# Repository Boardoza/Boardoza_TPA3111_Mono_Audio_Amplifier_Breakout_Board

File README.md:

# Boardoza TPA3111 Mono Audio Amplifier Breakout Board

The **Boardoza TPA3111 Mono Audio Amplifier Module** is a compact and efficient Class-D audio amplifier built around the **Texas Instruments TPA3111D1** chip. Designed to deliver up to **10W mono output power**, this board provides high-quality audio performance with minimal heat generation thanks to its high-efficiency architecture.

With a wide **8V to 28V DC input voltage range**, this amplifier module is compatible with a variety of power sources including DC adapters and battery systems. Screw terminal connections for power, audio input, and speaker output make installation quick and reliable. It is ideal for **DIY speaker builds, portable audio systems, embedded audio solutions, and custom sound projects** requiring compact and efficient amplification.

## [Click here to purchase!](https://www.ozdisan.com/ureticiler/boardoza)

| Front Side | Back Side |
|:---:|:---:|
|  |  |

---

## Key Features

- **High-Efficiency Class-D Amplifier:** 310 khz Switching frequency provides clear and powerful mono audio output with minimal heat generation.
- **Wide Input Voltage Range:** Operates from 8V to 28V DC, compatible with various power sources.
- **Easy Connectivity:** Screw terminals for audio input, speaker output, and power connections.
- **Clean Audio Performance:** Integrated pop and click suppression for smooth startup and shutdown.
- **Built-in Protection Features:** Includes thermal shutdown and short-circuit protection for reliable operation.

---

## Technical Specifications

**Model:** TPA3111D1  
**Manufacturer:** Boardoza   
**Manufacturer IC:** Texas Instruments   
**Input Voltage:** 8V – 28V DC  
**Functions:** Mono Audio Amplifier  
**Amplifier Type:** Class-D  
**Output Power:** Up to 10W  
**Efficiency:** Up to 90%  
**Audio Output:** Mono (H-Bridge)  
**Gain Setting:** Configurable via JP2 / JP3 (Default: 36 dB)  
**Protection Features:** Thermal protection, short-circuit protection  
**Operating Temperature:** -40 °C to +85 °C  
**Board Dimensions:** 40 mm x 40 mm  

---

## Board Pinout

### **( JP2 & JP3 ) Gain Configuration (GAIN1 / GAIN0)**

| Pin / Jumper | Pin Name | Description |
|:---:|:---:|---|
| JP2 | GAIN1 | Gain select input (logic level via jumper) |
| JP3 | GAIN0 | Gain select input (logic level via jumper) |

> Default configuration is typically **36 dB** (GAIN1=1, GAIN0=1).

#### **Gain / Input Impedance Selection Table**

| GAIN1 | GAIN0 | Amplifier Gain (dB) (Typical) | Input Impedance (kΩ) (Typical) |
|:---:|:---:|:---:|:---:|
| 0 | 0 | 20 | 60 |
| 0 | 1 | 26 | 30 |
| 1 | 0 | 32 | 15 |
| 1 | 1 | 36 | 9 |

---

### **( JP5 ) Control Pins**

| Pin Number | Pin Name | Description |
|:---:|:---:|---|
| 1 | SD | Shutdown pin (Active Low). Connect to FAULT for auto-recovery |
| 2 | FAULT | Fault indicator pin (Active Low). Connect to SD for auto-recovery |

---

### **( J3 ) Power Connector**

| Pin Number | Pin Name | Description |
|:---:|:---:|---|
| 1 | 8V–28V | DC Voltage Input |
| 2 | GND | Ground |

---

### **( J1 ) Audio Input**

| Pin Number | Pin Name | Description |
|:---:|:---:|---|
| 1 | IN+ | Positive audio input |
| 2 | IN- | Negative audio input |

---

### **( J2 ) Speaker Output**

| Pin Number | Pin Name | Description |
|:---:|:---:|---|
| 1 | OUT+ | Class-D H-Bridge positive output |
| 2 | OUT- | Class-D H-Bridge negative output |

---

## Board Dimensions

---

## Step Files

[Boardoza TPA3111.step](./assets/TPA3111%20Step.step)

---

## Datasheet

[TPA3111D1 Datasheet](./assets/TPA3111%20Datasheet.pdf)

---

## Version History

- **V1.0.0** – Initial Release

---

## Support

- If you have any questions or need support, please contact **support@boardoza.com**

---

## **License**
### **Hardware Design**

[![CC BY-SA 4.0][cc-by-sa-shield]][cc-by-sa]

All hardware design files are licensed under [Creative Commons Attribution-ShareAlike 4.0 International License][cc-by-sa].

[cc-by-sa]: http://creativecommons.org/licenses/by-sa/4.0/
[cc-by-sa-shield]: https://img.shields.io/badge/License-CC%20BY--SA%204.0-lightgrey.svg

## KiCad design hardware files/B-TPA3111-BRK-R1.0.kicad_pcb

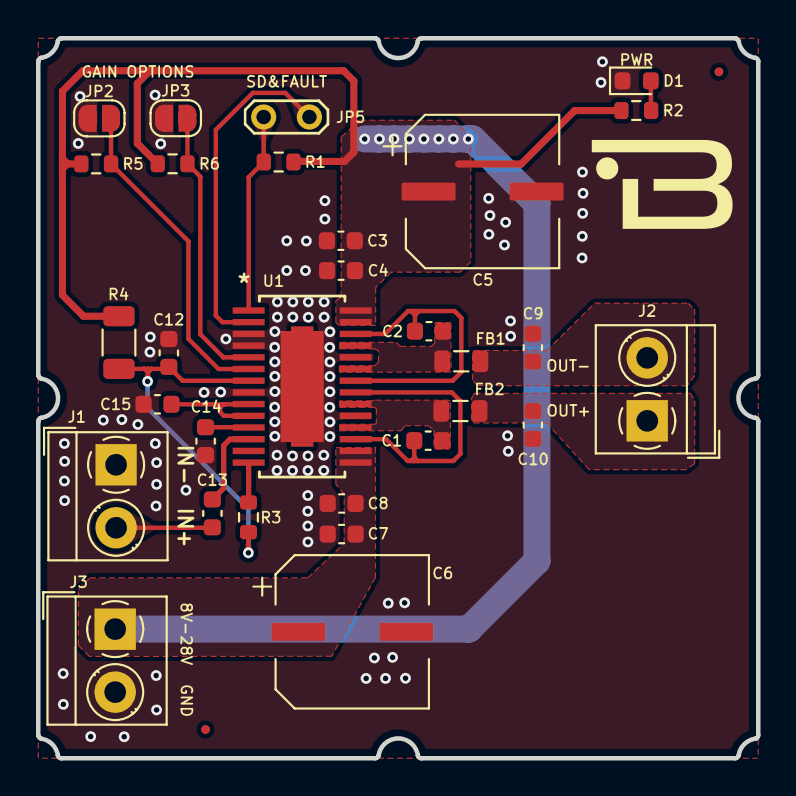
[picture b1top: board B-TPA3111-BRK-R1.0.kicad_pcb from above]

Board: 2 copper layers, 40.0 x 40.0 mm, 30 parts (0 on the bottom side), 19 nets.

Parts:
C1, C2: 0.47uF; C_0603_1608Metric
C3, C7: 0.1uF; C_0603_1608Metric
C4, C8, C9, C10: 1000pF; C_0603_1608Metric
C5, C6: 100uF; CP_Elec_8x10
C12, C13, C14, C15: 1uF; C_0603_1608Metric
D1: RED; LED_0603_1608Metric
FB1, FB2: 120R/100MHz; L_0805_2012Metric
J1, J2, J3: Screw_Terminal_01x02; TerminalBlock_MetzConnect_Type059_RT06302HBWC_1x02_P3.50mm_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
JP2, JP3: SolderJumper_2_Open; SolderJumper-2_P1.3mm_Open_RoundedPad1.0x1.5mm
JP5: Jumper_2_Open; TestPoint_2Pads_Pitch2.54mm_Drill0.8mm
R1, R3, R5, R6: 100K; R_0603_1608Metric
R2: 3K; R_0603_1608Metric
R4: 10R; R_1206_3216Metric
U1: TPA3111D1PWPR; PWP28_6P17X2P4-M

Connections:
/AVCC: C12.1, R3.1, R4.2, U1.7 (AVCC)
/GAIN0: JP3.1 (A), R6.1, U1.5 (GAIN0)
/GAIN1: JP2.1 (A), R5.1, U1.6 (GAIN1)
/GVDD: C15.1, U1.9 (GVDD), U1.10 (PLIMIT)
/INP: C13.2, U1.12 (INP)
/OUT+: C10.1, FB2.2, J2.1
/OUT-: C9.2, FB1.2, J2.2
/PVCC: C3.1, C4.1, C5.1, C6.1, C7.1, C8.1, J3.1, R1.1, R2.2, R4.1, R5.2, R6.2, U1.15 (PVCC), U1.16 (PVCC), U1.27 (PVCC), U1.28 (PVCC)
GND: C3.2, C4.2, C5.2, C6.2, C7.2, C8.2, C9.1, C10.2, C12.2, C14.1, C15.2, D1.1 (K), J1.1, J3.2, JP2.2 (B), JP3.2 (B), U1.3 (GND), U1.4 (GND), U1.8 (AGND), U1.19 (PGND), U1.24 (PGND), U1.29 (EPAD)
unnamed: C1.1, FB2.1, U1.18 (OUTP), U1.20 (OUTP)
unnamed: C1.2, U1.17 (BSP), U1.21 (BSP)
unnamed: C2.1, FB1.1, U1.23 (OUTN), U1.25 (OUTN)
unnamed: C2.2, U1.22 (BSN), U1.26 (BSN)
unnamed: D1.2 (A), R2.1
unnamed: C13.1, J1.2
unnamed: JP5.1 (A), U1.2 (*FAULT)
unnamed: JP5.2 (B), R1.2, U1.1 (*SD)
unnamed: R3.2, U1.14 (AVCC)
unnamed: C14.2, U1.11 (INN)
